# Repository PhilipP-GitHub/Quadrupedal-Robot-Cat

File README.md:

# Quadrupedal-Robot-Cat
A repo for a quadrupedal robot cat project. This project is under development.

# Peripherals & Features
  - Distance Sensors (VL53L0X)
  - SPI LCD Display (ILI9341)
  - 16 Channel PWM Controller (PCA9685)
  - I2S Microphone (SPH0645LM4H)
  - I2S Audio Amplifier (MAX98357)
  - Capacitive Touch Sensors
  - IMU / Accelerometer (optional)(MPU6050)
  - NRF24L01 Remote Control (NRF24L01)
  - Wi-Fi access (ESP-01)
  - SD Card

# Remote Controller
  - Joystick
  - NRF24L01 Module
  - IMU / Accelerometer (optional)(MPU6050)

# TO-DO 
The following drivers needs to be developed
  - [X] Distance Sensors (VL53L0X)
  - [X] LCD Display (ILI9341)
  - [ ] 16 Channel PWM Controller (PCA9685)
  - [ ] Analog Microphone
  - [X] FSMC SRAM
  - [X] Capacitive Touch Sensors
  - [X] PID Control for servos
  - [ ] IMU / Accelerometer (optional)(MPU6050)
  - [ ] NRF24L01 Remote Control (NRF24L01)
  - [ ] Wi-Fi access (ESP-01)
  - [X] SD Card Driver

# Development Roadmap
1. Develope all necessary mechanical components
Progress:
  - [X] Legs
  - [X] Back
  - [X] Neck & Head
    
2. Develope the joint motor driver
Progress:
  - [X] Schematic
  - [X] PCB Layout
  - [X] Order & Assembly

3. Develope the Mainboard
Progress:
  - [ ] Schematic
  - [ ] PCB Layout
  - [ ] Order & Assembly

4. Develope the low level firmwares
Progress:
  - [X] PWM generations (timers & PCA9685)
  - [X] PID Controls
  - [ ] NRF24L01 communciation
  - [ ] LCD driver to display bitmaps (DMA)
  - [ ] I2S Speaker to play audio file
  - [X] Distance sensors to read the distance
  - [ ] Leg trajectory planning

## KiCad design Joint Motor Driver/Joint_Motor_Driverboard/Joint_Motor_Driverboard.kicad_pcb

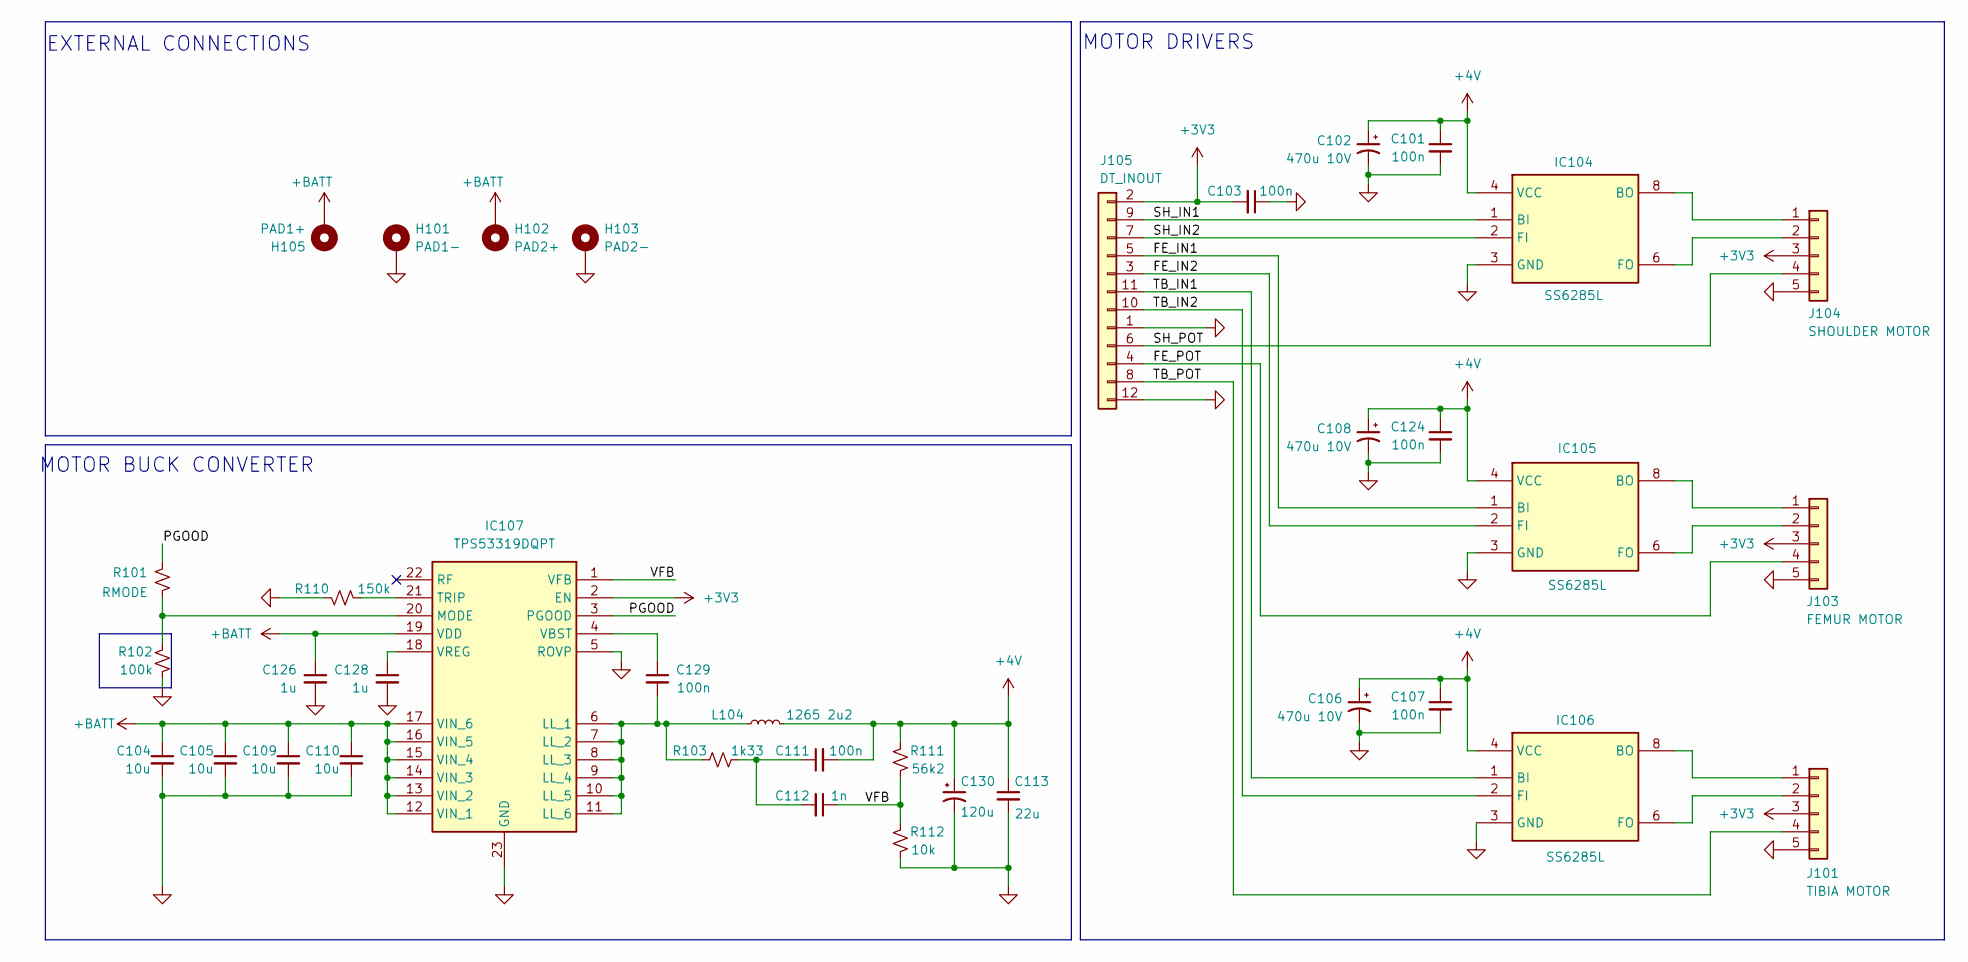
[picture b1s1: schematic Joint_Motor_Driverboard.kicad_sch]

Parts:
C101, C103, C107, C111, C124, C129: 100n; C_0805_2012Metric
C102, C106, C108: 470u 10V; CP_Radial_D6.3mm_P2.50mm
C104, C105, C109, C110: 10u; C_0805_2012Metric
C112: 1n; C_0805_2012Metric
C113: 22u; C_0805_2012Metric
C126, C128: 1u; C_0805_2012Metric
C130: 120u; CP_Radial_D5.0mm_P2.00mm
H101: PAD1-; MountingHole_4.3mm_M4_DIN965_Pad
H102: PAD2+; MountingHole_4.3mm_M4_DIN965_Pad
H103: PAD2-; MountingHole_4.3mm_M4_DIN965_Pad
H105: PAD1+; MountingHole_4.3mm_M4_DIN965_Pad
IC104, IC105, IC106: SS6285L; SOIC127P600X175-8N; Manufacturer_Part_Number RZ7889
IC107: TPS53319DQPT; SON50P500X600X150-23N-D; Manufacturer_Part_Number TPS53319DQPT; Mouser Part Number 595-TPS53319DQPT
J101: TIBIA MOTOR; JST_PH_S5B-PH-K_1x05_P2.00mm_Horizontal
J103: FEMUR MOTOR; JST_PH_S5B-PH-K_1x05_P2.00mm_Horizontal
J104: SHOULDER MOTOR; JST_PH_S5B-PH-K_1x05_P2.00mm_Horizontal
J105: DT_INOUT; PinHeader_2x06_P1.27mm_Vertical
L104: 1265 2u2; L_TaiTech_TMPC1265_13.5x12.5mm
R101: RMODE; R_0805_2012Metric
R102: 100k; R_0805_2012Metric
R103: 1k33; R_0805_2012Metric
R110: 150k; R_0805_2012Metric
R111: 56k2; R_0805_2012Metric
R112: 10k; R_0805_2012Metric

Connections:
+3V3: C103.2, IC107.2 (EN), J101.3, J103.3, J104.3, J105.2
+4V: C101.1, C102.1, C106.1, C107.1, C108.1, C111.2, C113.1, C124.1, C130.1, IC104.4 (VCC), IC105.4 (VCC), IC106.4 (VCC), L104.2, R111.1
+BATT: C104.1, C105.1, C109.1, C110.1, C126.1, H102.1, H105.1, IC107.12 (VIN_1), IC107.13 (VIN_2), IC107.14 (VIN_3), IC107.15 (VIN_4), IC107.16 (VIN_5), IC107.17 (VIN_6), IC107.19 (VDD)
/FE_IN1: IC105.1 (BI), J105.5
/FE_IN2: IC105.2 (FI), J105.3
/FE_POT: J103.4, J105.4
/PGOOD: IC107.3 (PGOOD), R101.2
/SH_IN1: IC104.1 (BI), J105.9
/SH_IN2: IC104.2 (FI), J105.7
/SH_POT: J104.4, J105.6
/TB_IN1: IC106.1 (BI), J105.11
/TB_IN2: IC106.2 (FI), J105.10
/TB_POT: J101.4, J105.8
/VFB: C112.1, IC107.1 (VFB), R111.2, R112.1
GND: C101.2, C102.2, C103.1, C104.2, C105.2, C106.2, C107.2, C108.2, C109.2, C110.2, C113.2, C124.2, C126.2, C128.2, C130.2, H101.1, H103.1, IC104.3 (GND), IC105.3 (GND), IC106.3 (GND), IC107.5 (ROVP), IC107.23 (GND), J101.5, J103.5, J104.5, J105.1, J105.12, R102.2, R110.2, R112.2
unnamed: C111.1, C112.2, R103.2
unnamed: IC104.7 (BO_1), IC104.8 (BO), J104.1
unnamed: IC104.5 (FO_1), IC104.6 (FO), J104.2
unnamed: IC105.7 (BO_1), IC105.8 (BO), J103.1
unnamed: IC105.5 (FO_1), IC105.6 (FO), J103.2
unnamed: IC106.7 (BO_1), IC106.8 (BO), J101.1
unnamed: IC106.5 (FO_1), IC106.6 (FO), J101.2
unnamed: C129.2, IC107.6 (LL_1), IC107.7 (LL_2), IC107.8 (LL_3), IC107.9 (LL_4), IC107.10 (LL_5), IC107.11 (LL_6), L104.1, R103.1
unnamed: IC107.20 (MODE), R101.1, R102.1
unnamed: IC107.21 (TRIP), R110.1
unnamed: C129.1, IC107.4 (VBST)
unnamed: C128.1, IC107.18 (VREG)

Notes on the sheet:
EXTERNAL CONNECTIONS
MOTOR BUCK CONVERTER
MOTOR DRIVERS

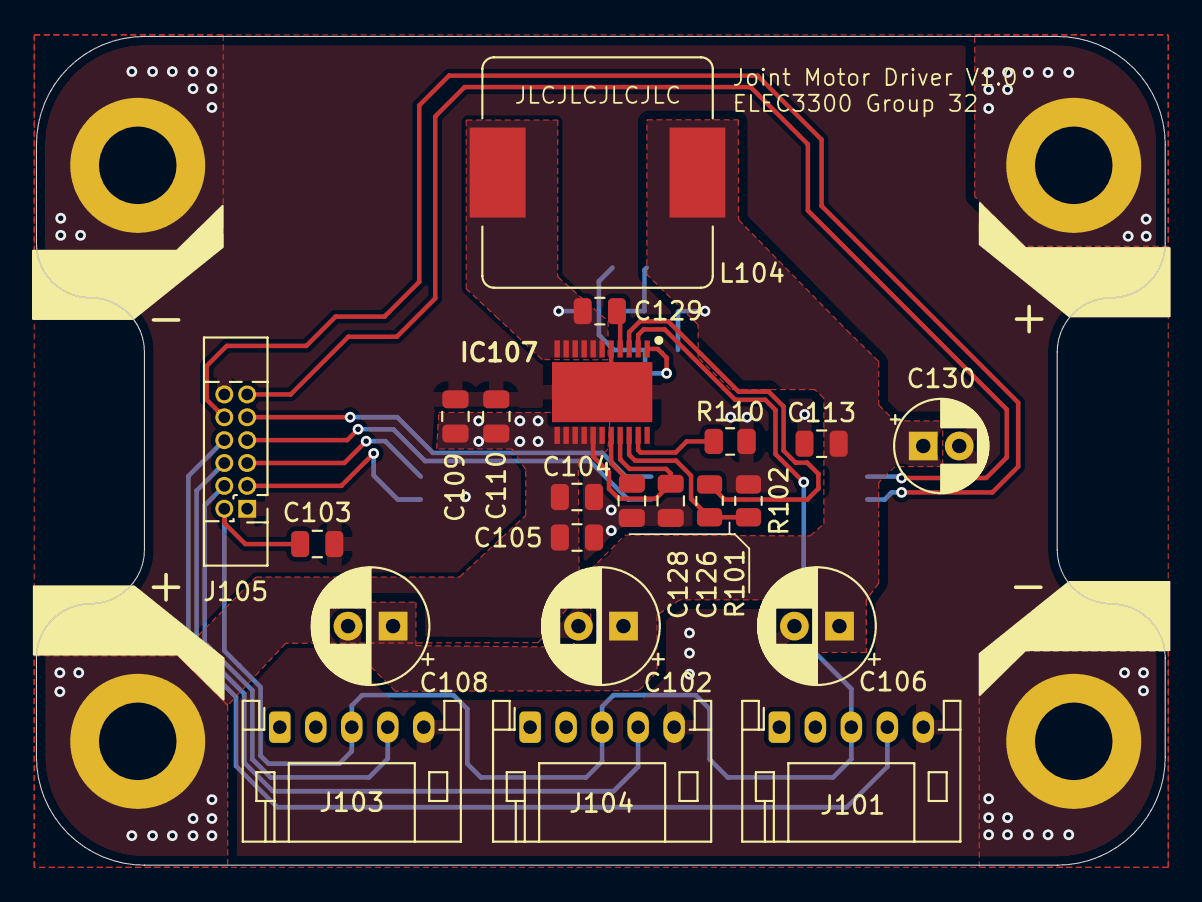
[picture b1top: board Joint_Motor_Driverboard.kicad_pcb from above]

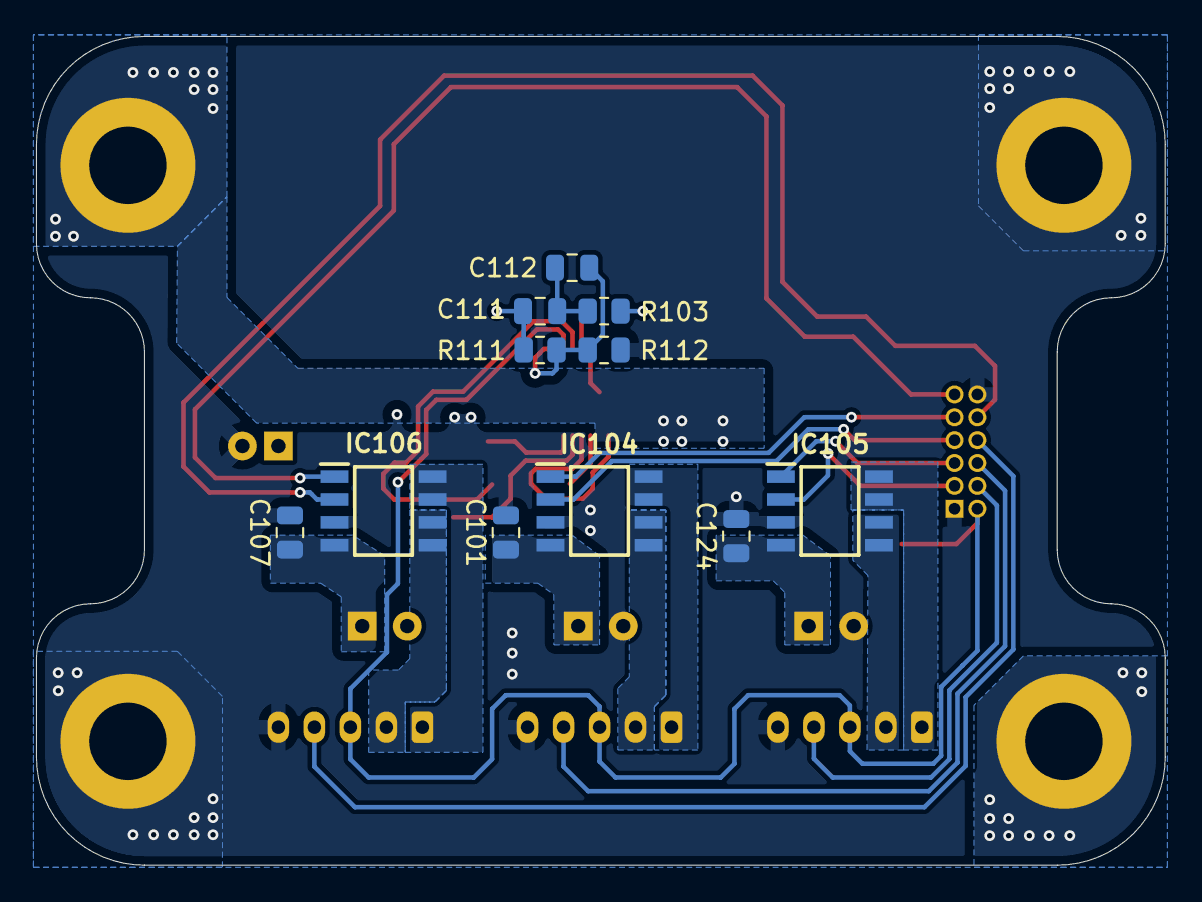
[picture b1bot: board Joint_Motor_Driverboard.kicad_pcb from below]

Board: 2 copper layers, 62.7 x 46.0 mm, 37 parts (11 on the bottom side), 27 nets.

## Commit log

2025-03-12 Added the 3D model files for the leg assembly parts
2025-03-12 Added the hardware files for the joint motor driver
2025-03-12 Relocated and renamed some files
2025-03-15 Commited a driver for the SD card
2025-04-10 Added an ADC library for reading servo motor angles
